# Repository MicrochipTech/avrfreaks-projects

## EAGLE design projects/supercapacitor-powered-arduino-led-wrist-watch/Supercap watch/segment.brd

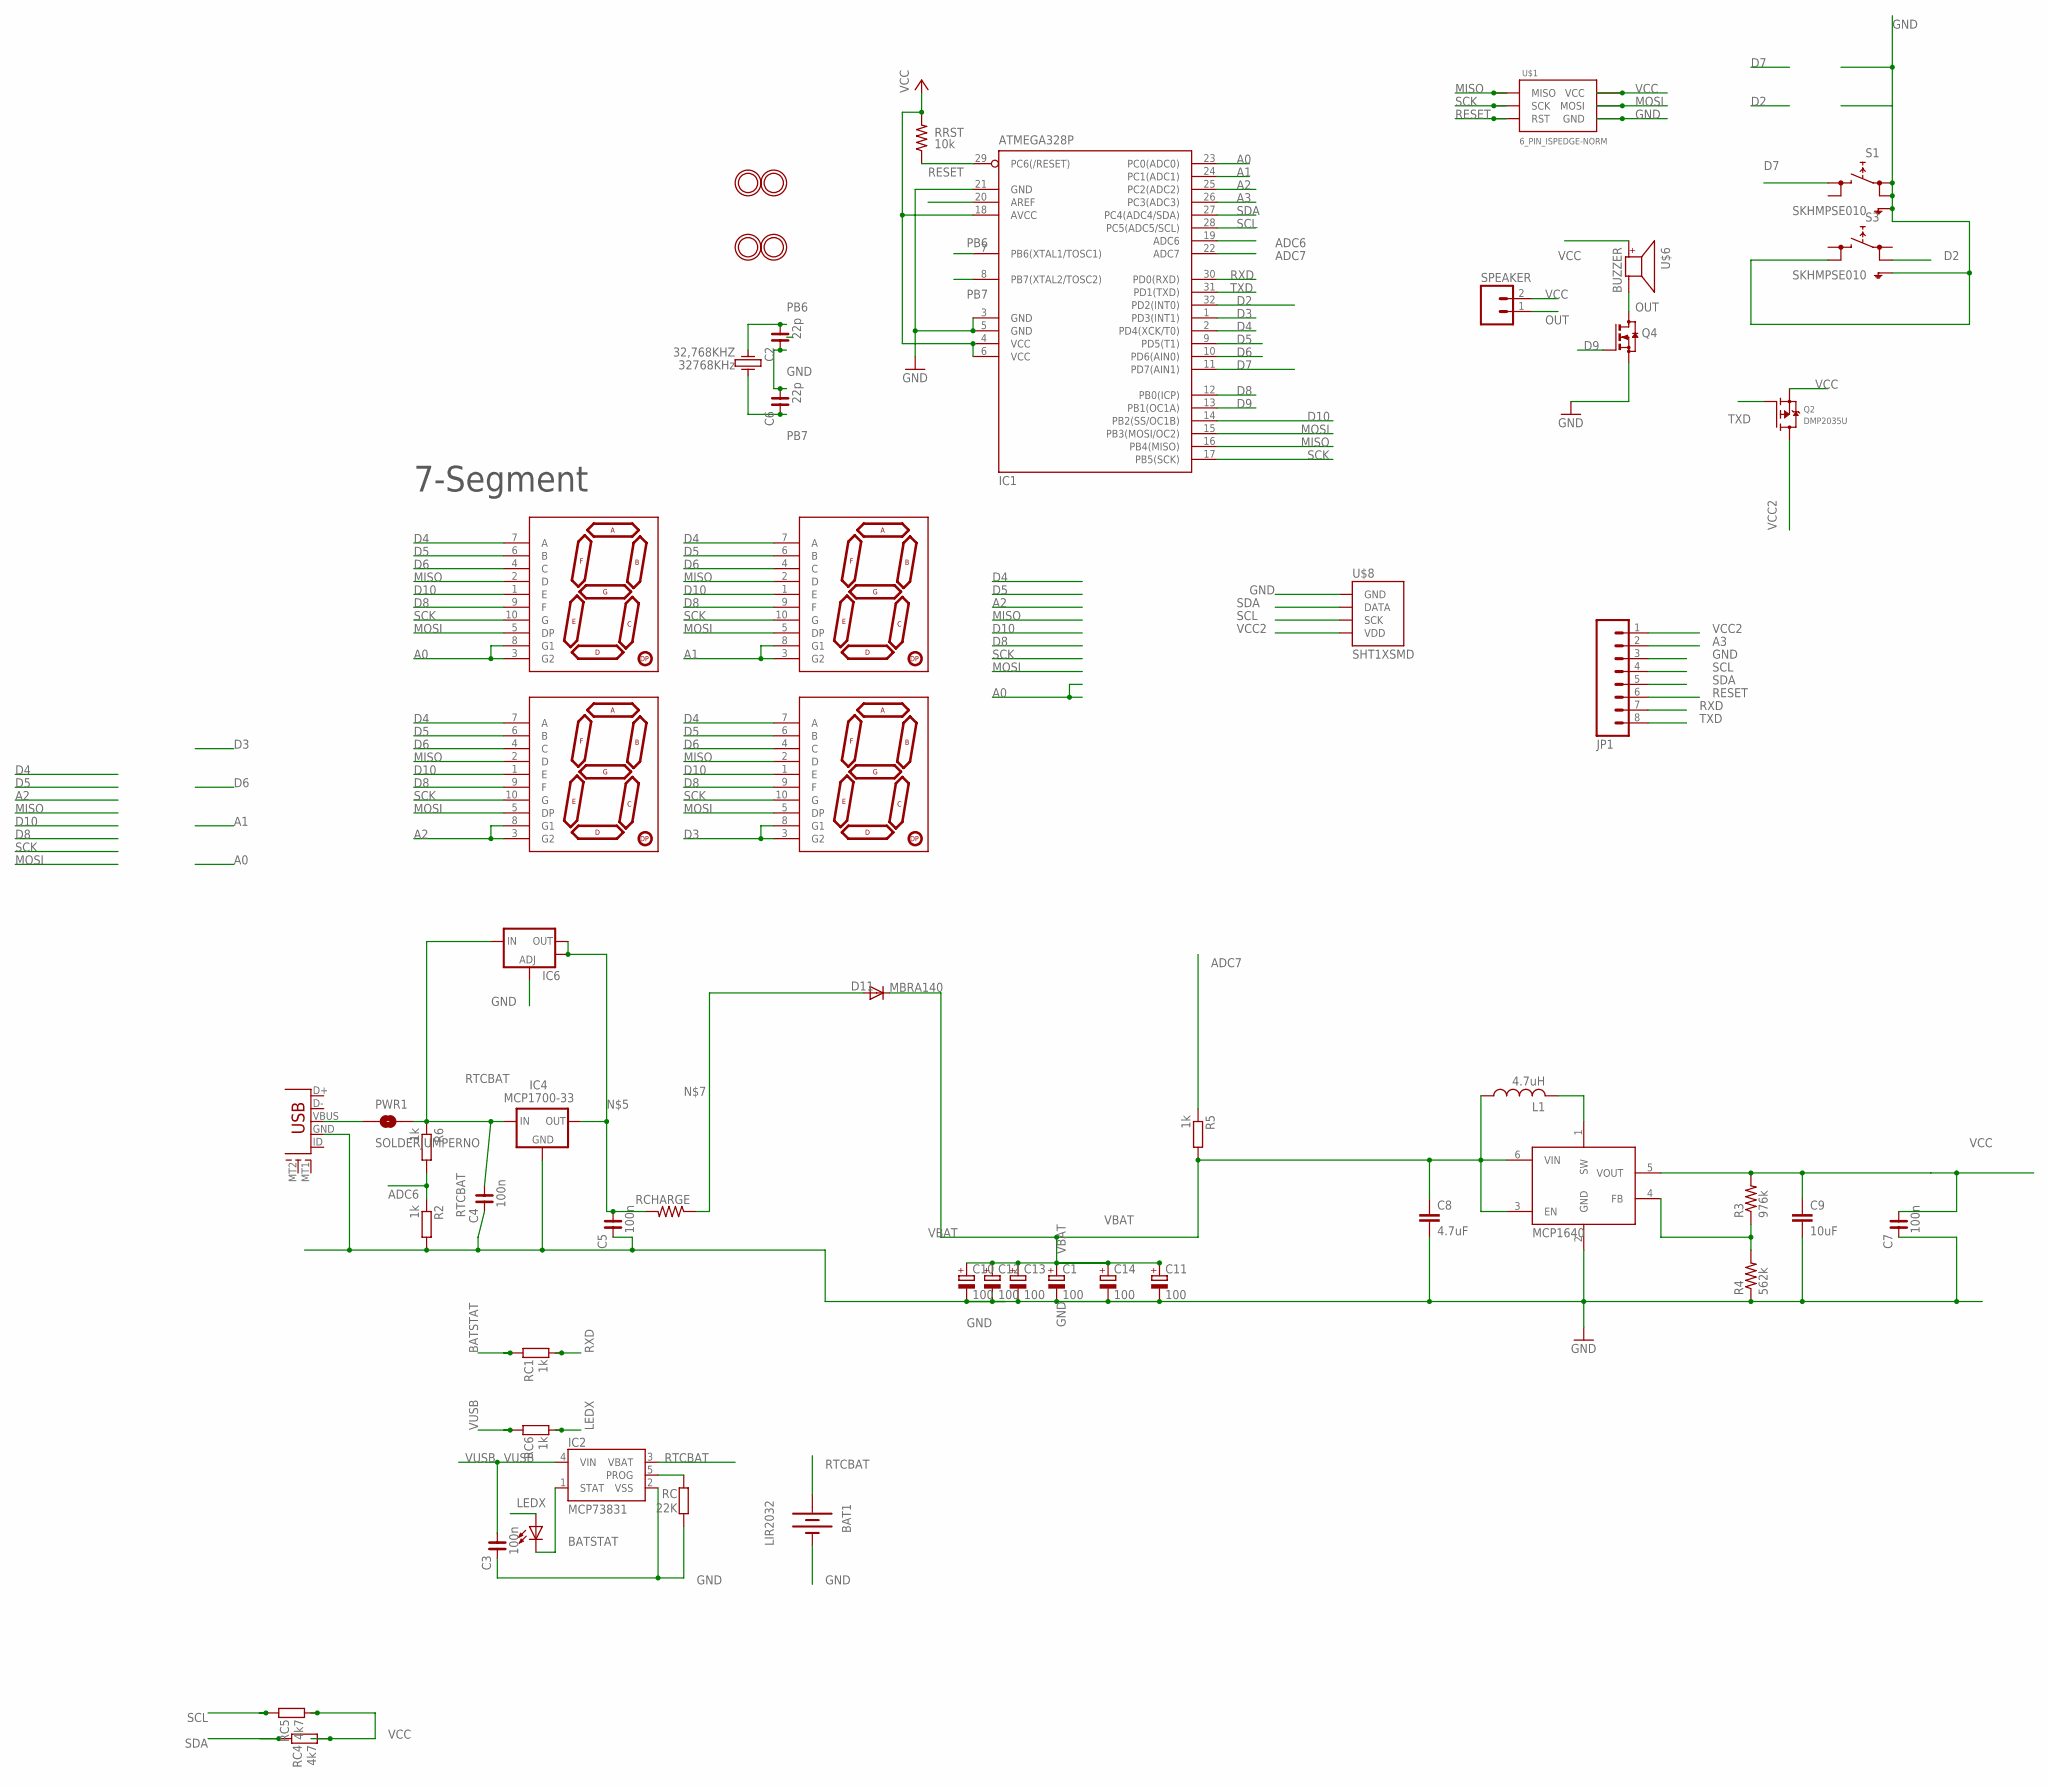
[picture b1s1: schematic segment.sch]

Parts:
32,768KHZ: 32768KHz; KX-327LT
BAT1: LIR2032; BATTCOM_20MM_PTH_SMT
C1, C10, C11, C12, C13, C14: 100; TT5D11L
C2, C6: 22p; C0603
C3, C4, C5, C7: 100n; C0603
C8: 4.7uF; 0805
C9: 10uF; 0805
CHG: 0805; CHIPLED_0603
D11: MBRA140; SOD-323
DIG1, DIG2, DIG3, DIG4: 7-SEGMENT-DISPLAY-1"-RED; 7-SEGMENT-SMD
IC1: ATMEGA328P; TQFP32-08
IC2: MCP73831; SOT23-5
IC4: MCP1700-33; SOT23
IC6: V_REG_LM1117SOT223; SOT223
JP1: M08NO_SILK; 1X08_PIN1_NO_SILK
L1: 4.7uH; LQH44
PWR1: SOLDERJUMPERNO; SJ_2S-NO
Q2: DMP2035U; SOT23-WIDE
Q4: BSS123; SOT23
R2, R5, R6: 1k; R0603
R3: 976k; 0603-RES
R4: 562k; 0603-RES
RC: 22K; R0603
RC1, RC6: 1k; R0603
RC4, RC5: 4k7; R0603
RCHARGE: RESISTOR1206; 1206
RRST: 10k; R0603@1
S1, S3: SKHMPSE010; SKHMPXE010
SPEAKER: M02PTH; 1X02
U2: MCP1640; SOT23-6
U$1: 6_PIN_ISPEDGE-NORM; 6_PIN_EDGE
U$2, U$3, U$4, U$5: MOUNTINGHOLE2.0; MOUNTINGHOLE_2.0_PLATED
U$6: BUZZER; SMT-8585-BUZZER
U$8: SHT1XSMD; SHT1X
USB2: USB-MICROBLARGEPAD; USB-MICROB_LARGEPAD

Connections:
A0: DIG1.3 (G2), DIG1.8 (G1), IC1.23 (PC0(ADC0))
A1: DIG2.3 (G2), DIG2.8 (G1), IC1.24 (PC1(ADC1))
A2: DIG3.3 (G2), DIG3.8 (G1), IC1.25 (PC2(ADC2))
A3: IC1.26 (PC3(ADC3)), JP1.2
ADC6: IC1.19 (ADC6), R2.1, R6.2
ADC7: IC1.22 (ADC7), R5.1
AREF: IC1.20 (AREF)
BATSTAT: CHG.C, IC2.1 (STAT), RC1.2
D2: IC1.32 (PD2(INT0)), S3.2 (1.2)
D3: DIG4.3 (G2), DIG4.8 (G1), IC1.1 (PD3(INT1))
D4: DIG1.7 (A), DIG2.7 (A), DIG3.7 (A), DIG4.7 (A), IC1.2 (PD4(XCK/T0))
D5: DIG1.6 (B), DIG2.6 (B), DIG3.6 (B), DIG4.6 (B), IC1.9 (PD5(T1))
D6: DIG1.4 (C), DIG2.4 (C), DIG3.4 (C), DIG4.4 (C), IC1.10 (PD6(AIN0))
D7: IC1.11 (PD7(AIN1)), S1.3 (2.1)
D8: DIG1.9 (F), DIG2.9 (F), DIG3.9 (F), DIG4.9 (F), IC1.12 (PB0(ICP))
D9: IC1.13 (PB1(OC1A)), Q4.1 (G)
D10: DIG1.1 (E), DIG2.1 (E), DIG3.1 (E), DIG4.1 (E), IC1.14 (PB2(SS/OC1B))
GND: BAT1.P$1 (-), C1.-, C2.2, C3.2, C4.2, C5.2, C6.1, C7.2, C8.2, C9.2, C10.-, C11.-, C12.-, C13.-, C14.-, IC1.3 (GND), IC1.5 (GND), IC1.21 (GND), IC2.2 (VSS), IC4.1 (GND), IC6.1 (ADJ), JP1.3, Q4.2 (S), R2.2, R4.1, RC.1, S1.1 (1.1), S1.2 (1.2), S1.5 (SH), S3.4 (2.2), S3.5 (SH), U2.2 (GND), U$1.6 (GND), U$8.1 (GND), USB2.GND
LEDX: CHG.A, RC6.1
MISO: DIG1.2 (D), DIG2.2 (D), DIG3.2 (D), DIG4.2 (D), IC1.16 (PB4(MISO)), U$1.1 (MISO)
MOSI: DIG1.5 (DP), DIG2.5 (DP), DIG3.5 (DP), DIG4.5 (DP), IC1.15 (PB3(MOSI/OC2)), U$1.4 (MOSI)
unnamed: IC2.5 (PROG), RC.2
unnamed: L1.P$2 (2), U2.1 (SW)
unnamed: C5.1, IC4.2 (OUT), IC6.2 (OUT), IC6.4 (OUT), RCHARGE.2
unnamed: R3.1, R4.2, U2.4 (FB)
unnamed: D11.2 (A), RCHARGE.1
OUT: Q4.3 (D), SPEAKER.1, U$6.-
PB6: 32,768KHZ.4, C2.1, IC1.7 (PB6(XTAL1/TOSC1))
PB7: 32,768KHZ.1, C6.2, IC1.8 (PB7(XTAL2/TOSC2))
RESET: IC1.29 (PC6(/RESET)), JP1.6, RRST.1, U$1.5 (RST)
RTCBAT: BAT1.P$2 (+), C4.1, IC2.3 (VBAT), IC4.3 (IN), IC6.3 (IN), PWR1.2, R6.1
RXD: IC1.30 (PD0(RXD)), JP1.7, RC1.1
SCK: DIG1.10 (G), DIG2.10 (G), DIG3.10 (G), DIG4.10 (G), IC1.17 (PB5(SCK)), U$1.3 (SCK)
SCL: IC1.28 (PC5(ADC5/SCL)), JP1.4, RC5.2, U$8.3 (SCK)
SDA: IC1.27 (PC4(ADC4/SDA)), JP1.5, RC4.2, U$8.2 (DATA)
TXD: IC1.31 (PD1(TXD)), JP1.8, Q2.1 (G)
VBAT: C1.+, C8.1, C10.+, C11.+, C12.+, C13.+, C14.+, D11.1 (C), L1.P$1 (1), R5.2, U2.3 (EN), U2.6 (VIN)
VCC: C7.1, C9.1, IC1.4 (VCC), IC1.6 (VCC), IC1.18 (AVCC), Q2.2 (S), R3.2, RC4.1, RC5.1, RRST.2, SPEAKER.2, U2.5 (VOUT), U$1.2 (VCC), U$6.+
VCC2: JP1.1, Q2.3 (D), U$8.4 (VDD)
VUSB: C3.1, IC2.4 (VIN), PWR1.1, RC6.2, USB2.VBUS

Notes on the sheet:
7-Segment

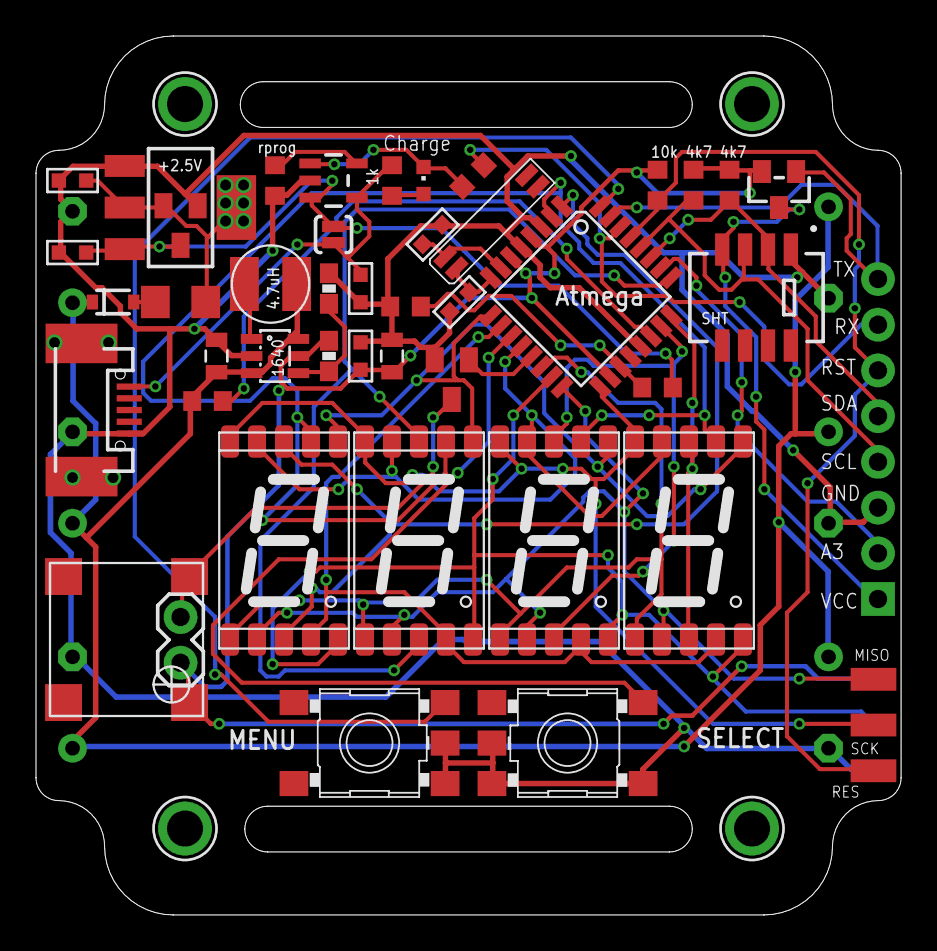
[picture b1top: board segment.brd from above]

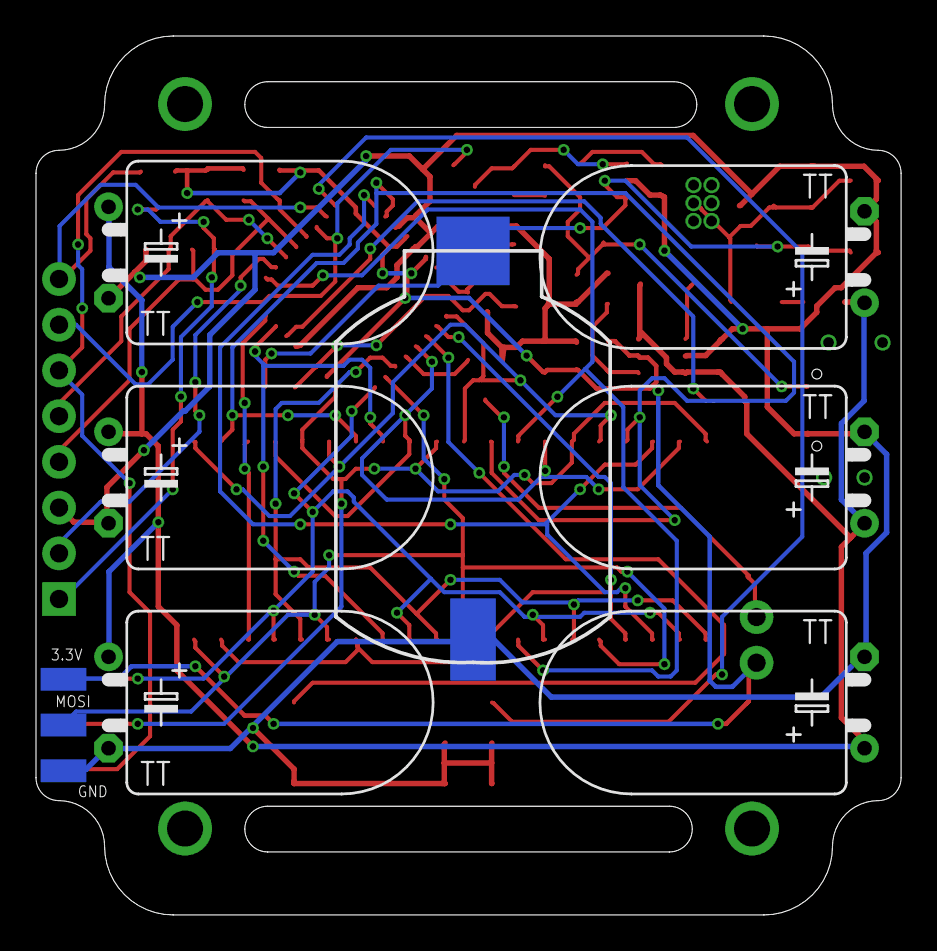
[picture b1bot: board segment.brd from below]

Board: 2 copper layers, 48.1 x 48.8 mm, 55 parts (7 on the bottom side), 39 nets.

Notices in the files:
parts and their libraries:
SparkFun: Licensing: CC v3.0 Share-Alike You are welcome to use this library for commercial purposes.
SparkFun-Sensors: Licensing: Creative Commons ShareAlike 4.0 International - https://creativecommons.org/licenses/by-sa/4.0
